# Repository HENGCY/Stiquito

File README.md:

# Stiquito
Projet Tutoré

Il faut toujours faire pull avant push 

command utile:

git clone https://github.com/HENGCY/Stiquito.git

git add <filename>

git commit -a -m "Message"

git push origin master

git pull

git push

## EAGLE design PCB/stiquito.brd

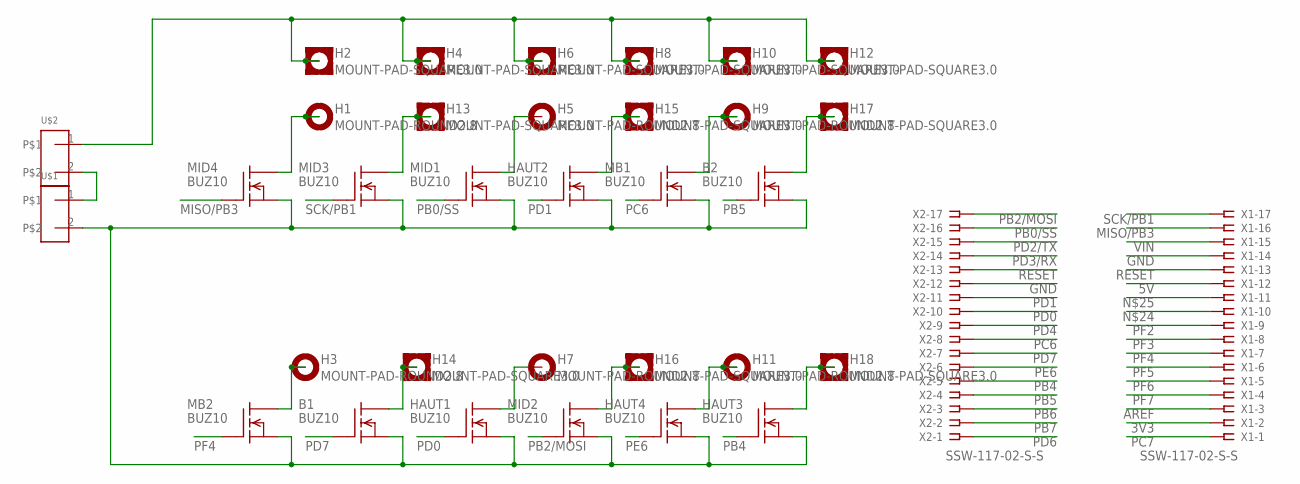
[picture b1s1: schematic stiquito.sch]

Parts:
B1, B2: BUZ10; TO220
H1, H3, H5, H7, H9, H11: MOUNT-PAD-ROUND2.8; 2,8-PAD
H2, H4, H6, H8, H10, H12, H13, H14, H15, H16, H17, H18: MOUNT-PAD-SQUARE3.0; 3,0-PAD-SQUARE
HAUT1, HAUT2, HAUT3, HAUT4: BUZ10; TO220
MB1, MB2: BUZ10; TO220
MID1, MID2, MID3, MID4: BUZ10; TO220
U$1, U$2: MOLEX_KK_2
X1, X2: SSW-117-02-S-S

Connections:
3V3: X1.2
5V: X1.12
AREF: X1.3
GND: B1.3 (S), B2.3 (S), HAUT1.3 (S), HAUT2.3 (S), HAUT3.3 (S), HAUT4.3 (S), MB1.3 (S), MB2.3 (S), MID1.3 (S), MID2.3 (S), MID3.3 (S), MID4.3 (S), U$1.2, X1.14, X2.12
MISO/PB3: MID4.1 (G), X1.16
unnamed: U$1.1, U$2.2
unnamed: H1.B2,8, MID4.2 (D)
unnamed: H13.B3,0, MID3.2 (D)
unnamed: B2.2 (D), H17.B3,0
unnamed: H9.B2,8, MB1.2 (D)
unnamed: H15.B3,0, HAUT2.2 (D)
unnamed: H5.B2,8, MID1.2 (D)
unnamed: H18.B3,0, HAUT3.2 (D)
unnamed: H11.B2,8, HAUT4.2 (D)
unnamed: H16.B3,0, MID2.2 (D)
unnamed: H7.B2,8, HAUT1.2 (D)
unnamed: B1.2 (D), H14.B3,0
unnamed: H3.B2,8, MB2.2 (D)
PB0/SS: MID1.1 (G), X2.16
PB2/MOSI: MID2.1 (G), X2.17
PB4: HAUT3.1 (G), X2.5
PB5: B2.1 (G), X2.4
PB6: X2.3
PB7: X2.2
PC6: MB1.1 (G), X2.8
PC7: X1.1
PD0: HAUT1.1 (G), X2.10
PD1: HAUT2.1 (G), X2.11
PD2/TX: X2.15
PD3/RX: X2.14
PD4: X2.9
PD6: X2.1
PD7: B1.1 (G), X2.7
PE6: HAUT4.1 (G), X2.6
PF2: X1.9
PF3: X1.8
PF4: MB2.1 (G), X1.7
PF5: X1.6
PF6: X1.5
PF7: X1.4
RESET: X1.13, X2.13
SCK/PB1: MID3.1 (G), X1.17
VIN: H2.B3,0, H4.B3,0, H6.B3,0, H8.B3,0, H10.B3,0, H12.B3,0, U$2.1, X1.15

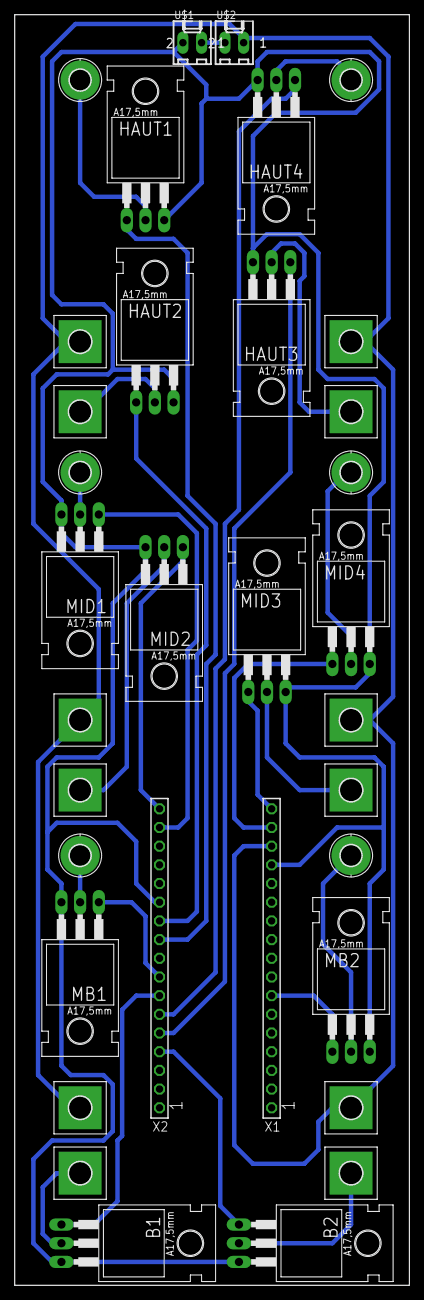
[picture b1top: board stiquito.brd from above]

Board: 2 copper layers, 53.6 x 172.7 mm, 34 parts (0 on the bottom side), 28 nets.

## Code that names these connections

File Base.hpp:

#include <Arduino.h>

// Constantes mapping
// Patte droite
#define RFF_PIN PD0  //18
#define RFU_PIN PD1  //19
#define RMF_PIN PB0  //8 
#define RMU_PIN PB2  //10
#define RBF_PIN PC6  //31
#define RBU_PIN PD7  //27

// Patte gauche
#define LFF_PIN PE6  //1   
#define LFU_PIN PB4  //28
#define LMF_PIN PB3  //11
#define LMU_PIN PB1  //9 
#define LBF_PIN PF4  //39 
#define LBU_PIN PB5  //29 

#define Init DDRB=DDRB|0b00111111;\
             DDRC=DDRC|0b01000000;\
             DDRD=DDRD|0b10000011;\
             DDRE=DDRE|0b01000000;\
             DDRF=DDRF|0b00010000;
/*           
             pinMode(RFF_PIN, OUTPUT);\
             pinMode(RFU_PIN, OUTPUT);\
             pinMode(RMF_PIN, OUTPUT);\
             pinMode(RMU_PIN, OUTPUT);\
             pinMode(RBF_PIN, OUTPUT);\
             pinMode(RBU_PIN, OUTPUT);\
             pinMode(LFF_PIN, OUTPUT);\
             pinMode(LFU_PIN, OUTPUT);\
             pinMode(LMF_PIN, OUTPUT);\
             pinMode(LMU_PIN, OUTPUT);\
             pinMode(LBF_PIN, OUTPUT);\
             pinMode(LBU_PIN, OUTPUT);
*/

typedef unsigned long FullState ;

// Etat actuel du stiquito
class Stiquito{
  public:
  Stiquito():FullState_((unsigned long)(0)),numero_etat_(0){};
  Stiquito(FullState state): FullState_(state),numero_etat_(0){};  
  //Constructeur de Stiquito

  void setState(FullState newState);
  //fonction de affectation des pin de Stiquito par modele de marche
  
  void execute(FullState Mode[],unsigned short temps);
  //fonction execution de programme en limitant de temps(pas tester)
  
  void showState(){Serial.println(FullState_);};
  //fonction de Serial.print pour afficher le current FullState_
  
  protected:
    FullState FullState_;
    //Il s'agit Etat Complete de Stiquito (4 Octet)
    //Compris 1 Octet de State RIGHT,1 Octet de State LEFT, 2 Octets pour holdTime 

    int numero_etat_;
    //Indication de numero etat en ce moment  
};

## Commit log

2017-03-22 Changed README.md
2017-03-22 code de Vivien
2017-03-22 File renamed
2017-03-22 Add PCB
2017-03-22 Modifie README.md
2017-03-22 testing
2017-03-29 [Code] Avancement | Probleme avec structures et macro construction d'etat
2017-05-03 Version teste en osscillopscope
2017-05-03 Added .gitignore
2017-05-03 Added gitignore
2017-05-03 Version de program execute marche
2017-05-10 Added python files
2017-05-17 Code python
2017-05-17 17/5
2017-05-17 Striquito
2017-05-17 17/5-Ecrire Registre
2017-05-29 ajout d'un modele de marche
2017-05-29 ajout de plusieurs modèles de marche
